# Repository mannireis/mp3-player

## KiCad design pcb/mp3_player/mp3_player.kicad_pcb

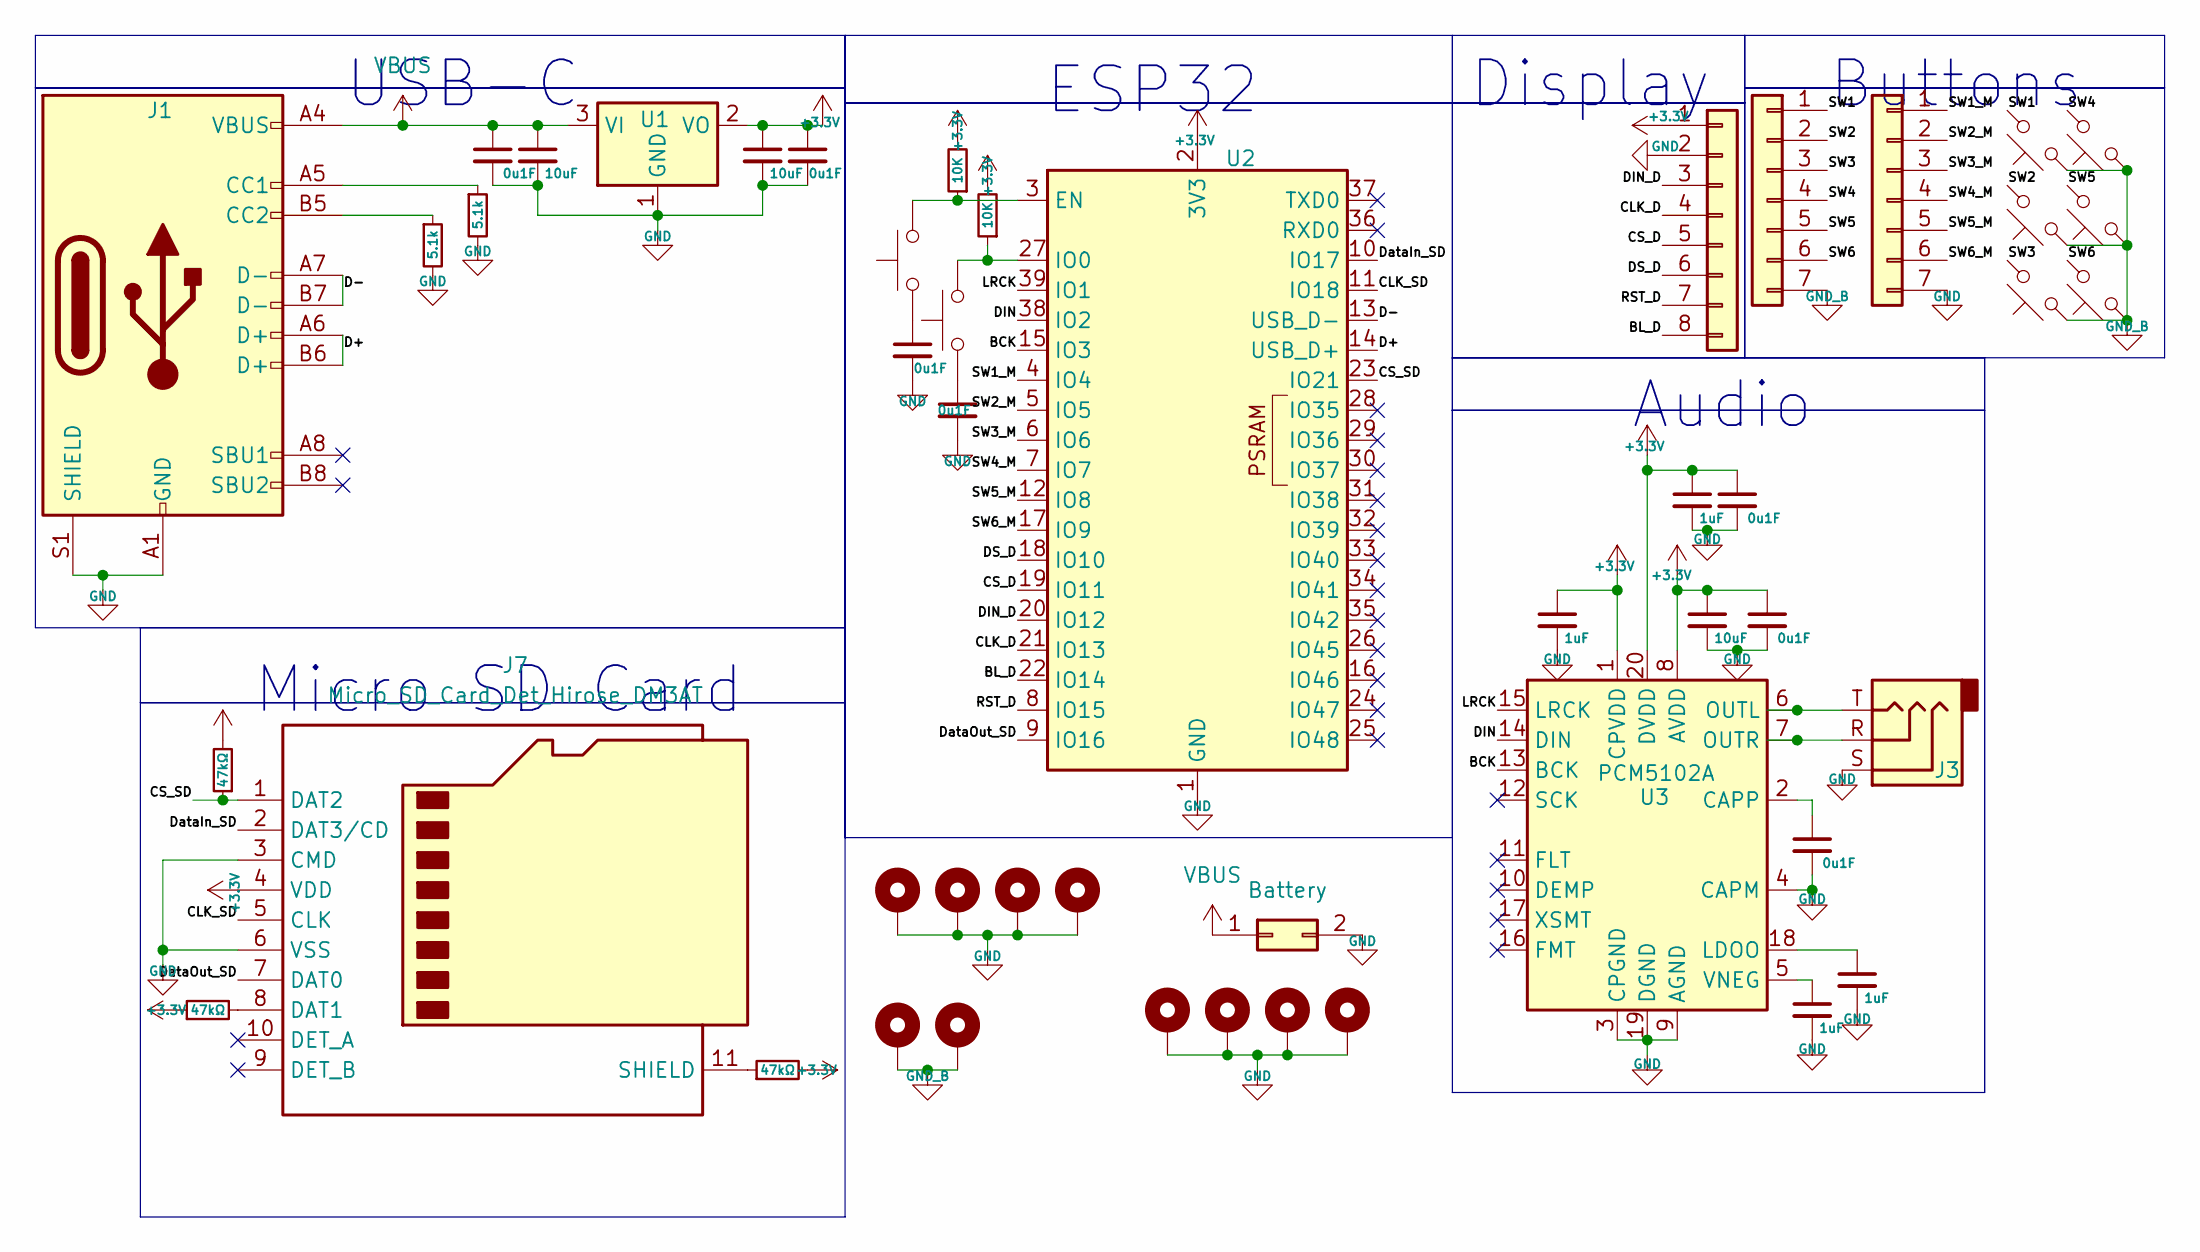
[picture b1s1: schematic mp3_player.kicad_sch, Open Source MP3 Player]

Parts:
C1, C3, C6, C8, C11, C13, C14: 0u1F; C_0603_1608Metric
C2, C4, C5: 10uF; C_0603_1608Metric
C7, C9, C10, C12: 1uF; C_0603_1608Metric
H1, H2, H3, H4, H5, H6, H7, H8, H9, H10: MountingHole_Pad; MountingHole_2.2mm_M2_Pad
J1: USB_C_Receptacle_USB2.0_16P; USB_C_Receptacle_HCTL_HC-TYPE-C-16P-01A
J2: Screen; JST_GH_SM08B-GHS-TB_1x08-1MP_P1.25mm_Horizontal
J3: AudioJack3; Jack_3.5mm_Lumberg_1503_02_Horizontal
J4, J5: Conn_01x07; connectorthatmeows
J6: Battery; PinHeader_1x02_P2.54mm_Vertical
J7: Micro_SD_Card_Det_Hirose_DM3AT; microSD_HC_Molex_104031-0811
R1, R2: 5.1k; R_0603_1608Metric
R3, R4, R5: 47kΩ; R_0603_1608Metric
R6, R7: 10K; R_0603_1608Metric
SW1, SW2, SW3, SW4, SW5, SW6: SW_Push_45deg; SW_Push_1P1T_NO_CK_KMR2
SW7, SW8: SW_Push; SW_Push_1P1T_NO_CK_KMR2
U1: AMS1117-3.3; SOT-223-3_TabPin2
U2: ESP32-S3-WROOM-1
U3: PCM5102A; TSSOP-20_4.4x6.5mm_P0.65mm

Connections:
+3.3V: C3.1, C4.1, C5.1, C6.1, C7.1, C8.1, C9.1, J2.1, J7.4 (VDD), R3.1, R4.2, R5.2, R6.2, R7.2, U1.2 (VO), U2.2 (3V3), U3.1 (CPVDD), U3.8 (AVDD), U3.20 (DVDD)
/BCK: U2.15 (IO3), U3.13 (BCK)
/BL_D: J2.8, U2.22 (IO14)
/CLK_D: J2.4, U2.21 (IO13)
/CLK_SD: J7.5 (CLK), U2.11 (IO18)
/CS_D: J2.5, U2.19 (IO11)
/CS_SD: J7.1 (DAT2), R5.1, U2.23 (IO21)
/D+: J1.A6 (D+), J1.B6 (D+), U2.14 (USB_D+)
/D-: J1.A7 (D-), J1.B7 (D-), U2.13 (USB_D-)
/DIN: U2.38 (IO2), U3.14 (DIN)
/DIN_D: J2.3, U2.20 (IO12)
/DS_D: J2.6, U2.18 (IO10)
/DataIn_SD: J7.2 (DAT3/CD), U2.10 (IO17)
/DataOut_SD: J7.7 (DAT0), U2.9 (IO16)
/LRCK: U2.39 (IO1), U3.15 (LRCK)
/RST_D: J2.7, U2.8 (IO15)
/SW1: J4.1, SW1.1
/SW1_M: J5.1, U2.4 (IO4)
/SW2: J4.2, SW2.1
/SW2_M: J5.2, U2.5 (IO5)
/SW3: J4.3, SW4.1
/SW3_M: J5.3, U2.6 (IO6)
/SW4: J4.4, SW3.1
/SW4_M: J5.4, U2.7 (IO7)
/SW5: J4.5, SW5.1
/SW5_M: J5.5, U2.12 (IO8)
/SW6: J4.6, SW6.1
/SW6_M: J5.6, U2.17 (IO9)
GND: C1.2, C2.2, C3.2, C4.2, C5.2, C6.2, C7.2, C8.2, C9.2, C10.2, C11.2, C12.2, C13.2, C14.2, H1.1, H2.1, H3.1, H4.1, H5.1, H6.1, H7.1, H8.1, J1.A1 (GND), J1.A12 (GND), J1.B1 (GND), J1.B12 (GND), J1.S1 (SHIELD), J2.2, J3.S, J5.7, J6.2, J7.3 (CMD), J7.6 (VSS), R1.2, R2.2, U1.1 (GND), U2.1 (GND), U2.40 (GND), U2.41 (GND), U3.3 (CPGND), U3.4 (CAPM), U3.9 (AGND), U3.19 (DGND)
GND_B: H9.1, H10.1, J4.7, SW1.2, SW2.2, SW3.2, SW4.2, SW5.2, SW6.2
unnamed: C13.1, SW8.1
unnamed: C14.1, SW7.1
unnamed: J1.A5 (CC1), R1.1
unnamed: J1.B5 (CC2), R2.1
unnamed: J7.8 (DAT1), R3.2
unnamed: J7.11 (SHIELD), R4.1
unnamed: R6.1, SW7.2, U2.3 (EN)
unnamed: R7.1, SW8.2, U2.27 (IO0)
unnamed: C11.1, U3.2 (CAPP)
unnamed: C10.1, U3.18 (LDOO)
unnamed: J3.T, U3.6 (OUTL)
unnamed: J3.R, U3.7 (OUTR)
unnamed: C12.1, U3.5 (VNEG)
VBUS: C1.1, C2.1, J1.A4 (VBUS), J1.A9 (VBUS), J1.B4 (VBUS), J1.B9 (VBUS), J6.1, U1.3 (VI)

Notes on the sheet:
Audio
ESP32
USB-C
Display
Buttons
Micro SD Card

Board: 2 copper layers, 49 parts (0 on the bottom side), 44 nets, no tracks yet.

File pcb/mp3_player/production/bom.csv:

Designator,Footprint,Quantity,Value,LCSC Part #
"C1, C11, C13, C14, C3, C6, C8",0603,7,0u1F,
"C10, C12, C7, C9",0603,4,1uF,
"C2, C4, C5",0603,3,10uF,
J1,USB_C_Receptacle_HCTL_HC-TYPE-C-16P-01A,1,USB_C_Receptacle_USB2.0_16P,
J2,JST_GH_SM08B-GHS-TB_1x08-1MP_P1.25mm_Horizontal,1,Screen,
J3,Jack_3.5mm_Lumberg_1503_02_Horizontal,1,AudioJack3,
"J4, J5",connectorthatmeows,2,Conn_01x07,
J6,PinHeader_1x02_P2.54mm_Vertical,1,Battery,
J7,microSD_HC_Molex_104031-0811,1,Micro_SD_Card_Det_Hirose_DM3AT,
"R1, R2",0603,2,5.1k,
"R3, R4, R5",0603,3,47kΩ,
"R6, R7",0603,2,10K,
"SW1, SW2, SW3, SW4, SW5, SW6",SW_Push_1P1T_NO_CK_KMR2,6,SW_Push_45deg,
"SW7, SW8",SW_Push_1P1T_NO_CK_KMR2,2,SW_Push,
U1,SOT-223-3_TabPin2,1,AMS1117-3.3,
U2,ESP32-S3-WROOM-1,1,ESP32-S3-WROOM-1,
U3,TSSOP-20_4.4x6.5mm_P0.65mm,1,PCM5102A,
